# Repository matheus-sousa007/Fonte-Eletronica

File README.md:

# Projetos da matéria SCC0180 - Eletrônica para Computação
No currículo da matéria SCC0180 consta 2 projetos
- Projeto 1: Fonte
- Projeto 2: Arduino

Este repositório servirá como local para agregar os projetos do grupo

# Participantes do Grupo
[Matheus Ventura de Sousa](https://github.com/matheusvdes007)
[João Guilherme Jarochinski Marinho](https://github.com/jj-marinho)

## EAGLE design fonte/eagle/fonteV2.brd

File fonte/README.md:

## Objetivo do Projeto
Desenvolver uma fonte elétrica capaz de fornecer energia para pequenos projetos de eletrônica, como projetos de Arduino.
Por conta disso ela deve seguir os critérios a seguir

## Critérios da Fonte
- Componentes elétricos simples
- Tensão Ajustável através de um potenciômetro (3v - 12v)
- Corrente de 100mA

## Precificação dos Componentes
| Componente                      | Quantidade | Preço   | Link                                                                            |
|---------------------------------|------------|---------|---------------------------------------------------------------------------------|
| Transformador 127/220AC -> 15v  | 1          | R$33,15 | [aqui](https://www.baudaeletronica.com.br/transformador-trafo-1a-15v-15v.html)  |
| Diodo Zener 1N4743 13v          | 1          | RS 0,35 | [aqui](https://www.mamuteeletronica.com.br/diodo-zener-1n4743-13v-1w-do-41)     |
| Ponte Retificadora 10A 100V     | 1          | R$ 6,66 | [aqui](https://www.casadoresistor.com.br/ponte-retificadora-10a-1000v-zcdp0003-p4727)|
| Potenciômetro Linear 5k R       | 1          | R$ 1,09 | [aqui](https://www.baudaeletronica.com.br/potenciometro-linear-de-5k-5000.html) |
| Transistor NPN 2N222            | 1          | R$ 0,35 | [aqui](https://www.autocorerobotica.com.br/2n222-transistor-npn)                |
| Capacitor 470uf                 | 1          | R$ 1,00 | [aqui](https://www.tecnotronics.com.br/capacitor-eletrolitico-470uf-25v.html)   |
| Resistor 2.5k                   | 1          | R$ 0,08 | [aqui](https://www.baudaeletronica.com.br/resistor-2k-5-1-4w.html)              |
| Resistor 1K                     | 1          | R$ 0,08 | [aqui](https://www.baudaeletronica.com.br/resistor-1k-5-1-4w.html)              |
| Resistor 120R                   | 1          | R$ 0,08 | [aqui](https://www.baudaeletronica.com.br/resistor-120r-5-1-4w.html)            |
| Resistor 2K                     | 1          | R$ 0,08 | [aqui](https://www.baudaeletronica.com.br/resistor-2K-5-1-4w.html)              |
| LED Difuso Vermelho             | 1          | R$ 0,24 | [aqui](https://www.baudaeletronica.com.br/led-difuso-5mm-vermelho.html)         |
| Total                           |            | R$43,16 |                                                                                 |
## Circuito no Falstad

- Link para o circuito: http://tinyurl.com/yaalcqcl

## Detalhes do Circuito
### [Video sobre Projeto](https://youtu.be/0voirnk2L9U)
- OBS: Durante a apresentação houveram algumas mudanças
	- Mudança do Resistor do Led para 2K (Impede o LED de queimar)
	- Mudança do Resistor do Zener para 1K (Faz com que menos corrente seja perdida no Diodo Zener)

### Justificativa para os componentes da fonte

#### Ponte Retificadora:
- A ponte de diodos foi introduzida ao circuito para que ele aproveite, tanto o ciclo positivo quanto negativo do circuito, além de impedir a circulação da tensão reversa, que poderia queimar os componentes.

#### Diodo Zener (1N4743):
- Esse diodo foi introduzido ao circuito para estabilizar a tensão na fonte, transformando-a em corrente contínua. Seu valor de tensão de ruptura é de 13 volts, para que a tensão final, que será introduzida na saída (ou carga) seja um valor muito próximo, se não for exato, de 12V.

#### Capacitor (470uF):
-  O capacitor serve para reduzir a variação da corrente alternada que vem do transformador. Sua capacitância, além de ser diretamente proporcional a intensidade de corrente elétrica, ela determina a velocidade de descarregamento do capacitor. Seu valor foi escolhido para deixar a corrente elétrica em um valor considerável para o regulador controlar, para chegar, no máximo, até a I = 100mA com uma margem de erro de 5% para mais.

#### Fonte A.C.: 
- A fonte que foi implantada no circuito representa a tomada. Ela tem a tensão eficaz de 127V.

#### Transformador: 
- O transformador implantado no circuito possui a razão de 15V/127V. O transformador recebe 127V como entrada e transforma essa tensão em 15V. As duas tensões podem ser entendidas como a tensão eficaz recebida e transformada. Essa razão pode ser entendida também como o número de espiras em cada bobina do transformador. O denominador da razão, que se refere a tensão recebida, pode ser relacionado como um múltiplo do número de espiras da 1ª bobina e, de maneira análoga, o númerador pode ser relacionado com a 2ª bobina.

#### Potenciômetro (5k Ohms): 
- O potenciômetro, com a função de regular a tensão e a corrente elétrica no circuito, foi escolhido com 5k Ohms pois esse é o valor adequado para que a tensão na saída varie entre 3V e 12V.

#### Resistor 1 (1k Ohms): 
- O resistor 1 foi aplicado ao circuito para proteger o diodo zener. Caso o resistor não fosse colocado, haveria a possibilidade de passar uma corrente infinita pelo diodo. Assim, o diodo queimaria. O valor do resistor é de 1000 Ohms para que o diodo não queime, assim, controlando a corrente elétrica.

#### Resistor 2 (2500 Ohms): 
O resistor 2 foi aplicado ao circuito para que, quando o potenciômetro fique no máximo, a tensão na saída fique muito próximo, se não exato, da tensão mínima de saída. O valor de 2.5k Ohms foi escolhido pois é o valor mais adequado para o resistor. Esse valor permite que a tensão minima de saída seja 3V.

#### LED Vermelho (2V - 2.5V): 
- O LED foi acrescentado ao circuito para ver se a saída do circuito está sendo alimentada com energia ou não. O LED vermelho foi escolhido devido a sua baixa tensão pois é possivel ter uma melhor visibilidade de sua luz quando o potenciômetro está regulado no mínimo.

#### Resistor 3 (2.2k Ohms): 
- O resistor 3 foi aplicado ao circuito para proteger o LED vermelho. O valor de 2200 Ohms foi escolhido para que o LED não queime com uma corrente muito alta.

#### Resistor 4 (120 Ohms): 
- O resistor 4 foi aplicado ao circuito para representar a saída. O resistor apresentado possui 120 Ohms pois é a resistência mais adequada para que o circuito conceda a saída uma corrente de, no máximo, I = 100mA e uma voltagem que varia entre 3V a 12V.

#### Transisor NPN (2N222): 
- O transistor NPN foi aplicado ao circuito para que ele possa atuar como amplificador de corrente elétrica. O tipo 2N222 foi escolhido para que o transistor do circuito não queimasse com facilidade.
 
## EAGLE - Esquemático e PCB
### Esquemático

### PCB

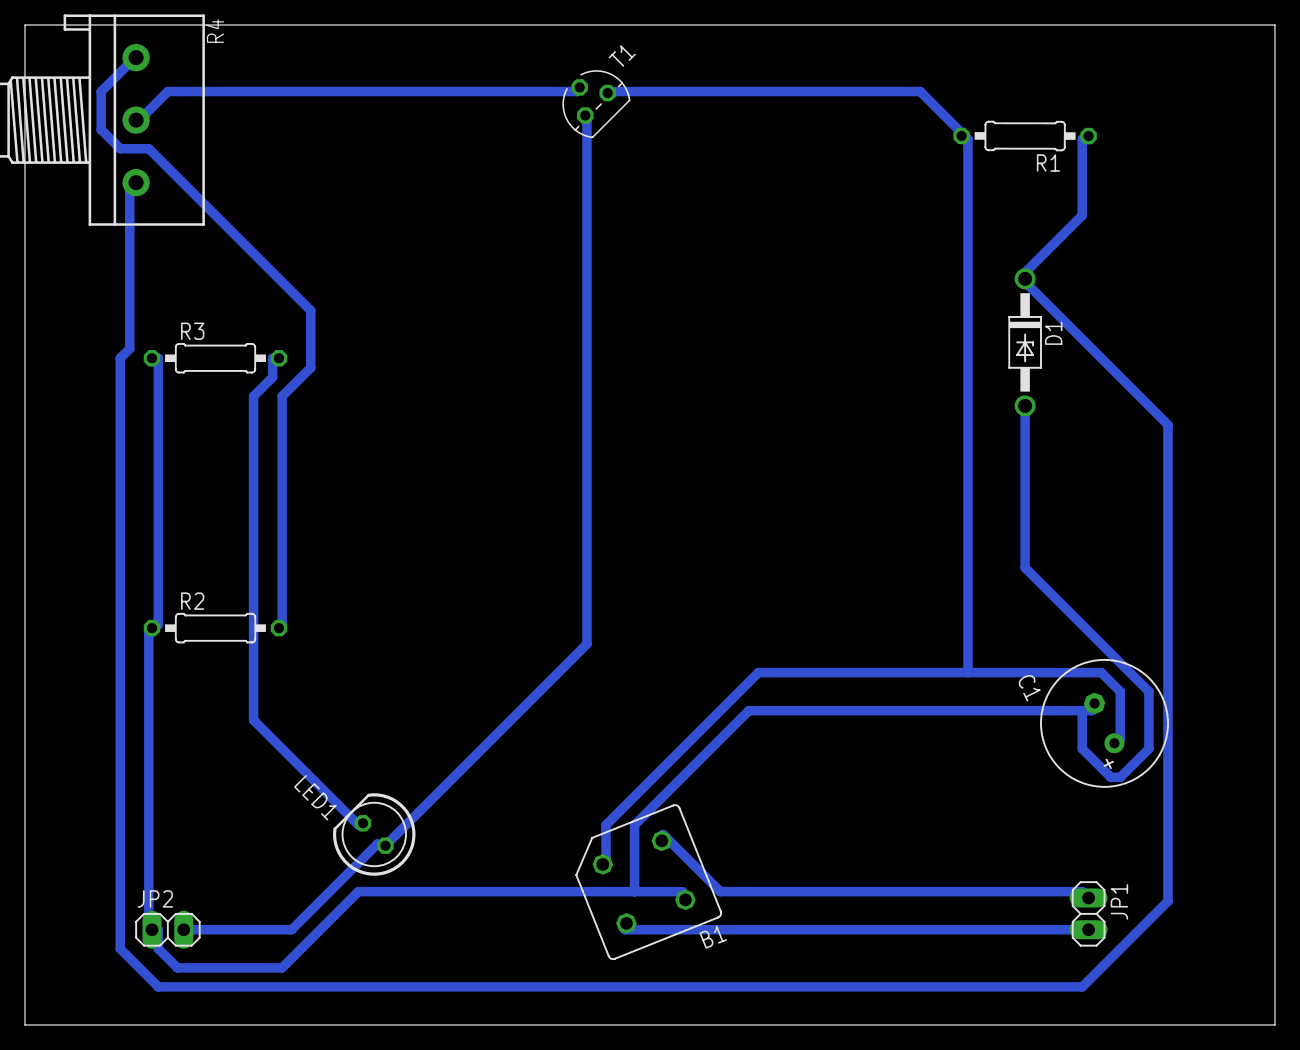
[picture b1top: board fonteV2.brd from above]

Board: 2 copper layers, 100.0 x 80.0 mm, 11 parts (0 on the bottom side), 9 nets.

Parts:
B1: 1KAB
C1: E3,5-10
D1: 1N4728; DO41Z10
JP1, JP2: 1X02
LED1: LED5MM
R1, R2, R3: 0207/10
R4: 3RP/1610N
T1: 2N3904; TO92

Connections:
unnamed: R2.2, R4.1
unnamed: B1.AC2, JP1.2
unnamed: B1.AC1, JP1.1
unnamed: B1.+, C1.+, R1.2, T1.1
unnamed: B1.-, C1.-, D1.A, JP2.1, R2.1, R3.1
unnamed: D1.C, R1.1, R4.3
unnamed: R4.2, T1.2
unnamed: JP2.2, LED1.A, T1.3
unnamed: LED1.K, R3.2

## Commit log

2020-07-14 Atualizando trabalho da fonte eletronica
2020-07-14 Atualizando o projeto da fonte
2020-07-14 Atualizando o projeto da fonte]
